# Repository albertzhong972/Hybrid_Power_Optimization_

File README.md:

# Hybrid-Power-Optimization
ECEN 404 Senior Design - Hybrid Power Optimization

Project Description:
We are combining DC power from a solar panel with AC power from the grid to provide power to a load. We are using a PIC32MK microcontroller in this project.

There are four subsystems:
  -Power (Antonio)
  -PCB (Albert)
  -Software/Firmware (Eduardo)
  -Feedback (Heraclio)

  You can find our individual work as well as our progress reports in our own folders.

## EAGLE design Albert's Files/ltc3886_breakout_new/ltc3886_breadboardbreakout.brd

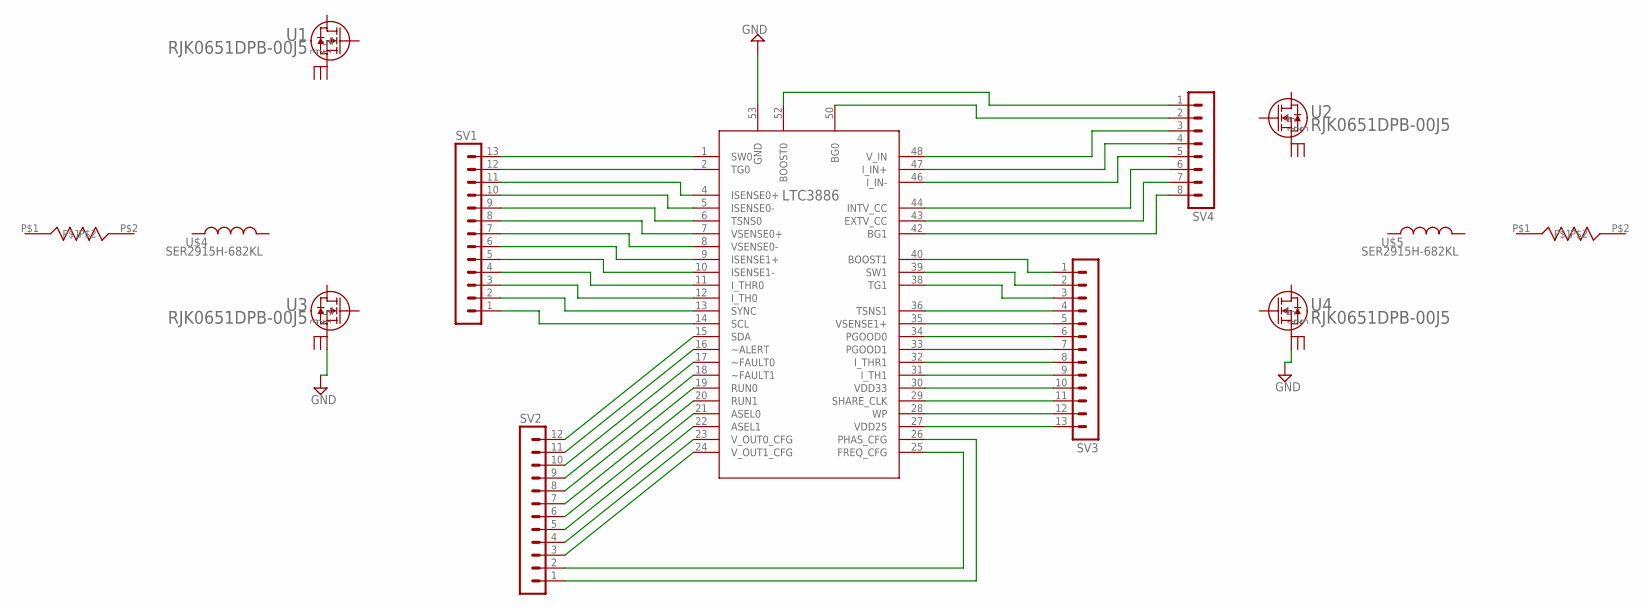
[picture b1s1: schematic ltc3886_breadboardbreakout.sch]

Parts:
GND: LTC3886; QFN-52_UKG_2
SV1, SV3: MA13-1
SV2: MA12-1
SV4: MA08-1
U1, U2, U3, U4: RJK0651DPB-00J5; LFPAK
U$2, U$3: CSS2H-2512K-2L00FE
U$4, U$5: SER2915H-682KL

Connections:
GND: GND.53 (GND), U3.1, U4.1
unnamed: GND.1 (SW0), SV1.13
unnamed: GND.2 (TG0), SV1.12
unnamed: GND.4 (ISENSE0+), SV1.11
unnamed: GND.5 (ISENSE0-), SV1.10
unnamed: GND.6 (TSNS0), SV1.9
unnamed: GND.7 (VSENSE0+), SV1.8
unnamed: GND.8 (VSENSE0-), SV1.7
unnamed: GND.9 (ISENSE1+), SV1.6
unnamed: GND.10 (ISENSE1-), SV1.5
unnamed: GND.11 (I_THR0), SV1.4
unnamed: GND.12 (I_TH0), SV1.3
unnamed: GND.13 (SYNC), SV1.2
unnamed: GND.14 (SCL), SV1.1
unnamed: GND.24 (V_OUT1_CFG), SV2.3
unnamed: GND.23 (V_OUT0_CFG), SV2.4
unnamed: GND.22 (ASEL1), SV2.5
unnamed: GND.21 (ASEL0), SV2.6
unnamed: GND.20 (RUN1), SV2.7
unnamed: GND.19 (RUN0), SV2.8
unnamed: GND.18 (~FAULT1), SV2.9
unnamed: GND.17 (~FAULT0), SV2.10
unnamed: GND.16 (~ALERT), SV2.11
unnamed: GND.15 (SDA), SV2.12
unnamed: GND.25 (FREQ_CFG), SV2.2
unnamed: GND.26 (PHAS_CFG), SV2.1
unnamed: GND.27 (VDD25), SV3.13
unnamed: GND.28 (WP), SV3.12
unnamed: GND.29 (SHARE_CLK), SV3.11
unnamed: GND.30 (VDD33), SV3.10
unnamed: GND.31 (I_TH1), SV3.9
unnamed: GND.32 (I_THR1), SV3.8
unnamed: GND.33 (PGOOD1), SV3.7
unnamed: GND.34 (PGOOD0), SV3.6
unnamed: GND.35 (VSENSE1+), SV3.5
unnamed: GND.36 (TSNS1), SV3.4
unnamed: GND.38 (TG1), SV3.3
unnamed: GND.39 (SW1), SV3.2
unnamed: GND.40 (BOOST1), SV3.1
unnamed: GND.42 (BG1), SV4.8
unnamed: GND.43 (EXTV_CC), SV4.7
unnamed: GND.44 (INTV_CC), SV4.6
unnamed: GND.46 (I_IN-), SV4.5
unnamed: GND.47 (I_IN+), SV4.4
unnamed: GND.48 (V_IN), SV4.3
unnamed: GND.50 (BG0), SV4.2
unnamed: GND.52 (BOOST0), SV4.1

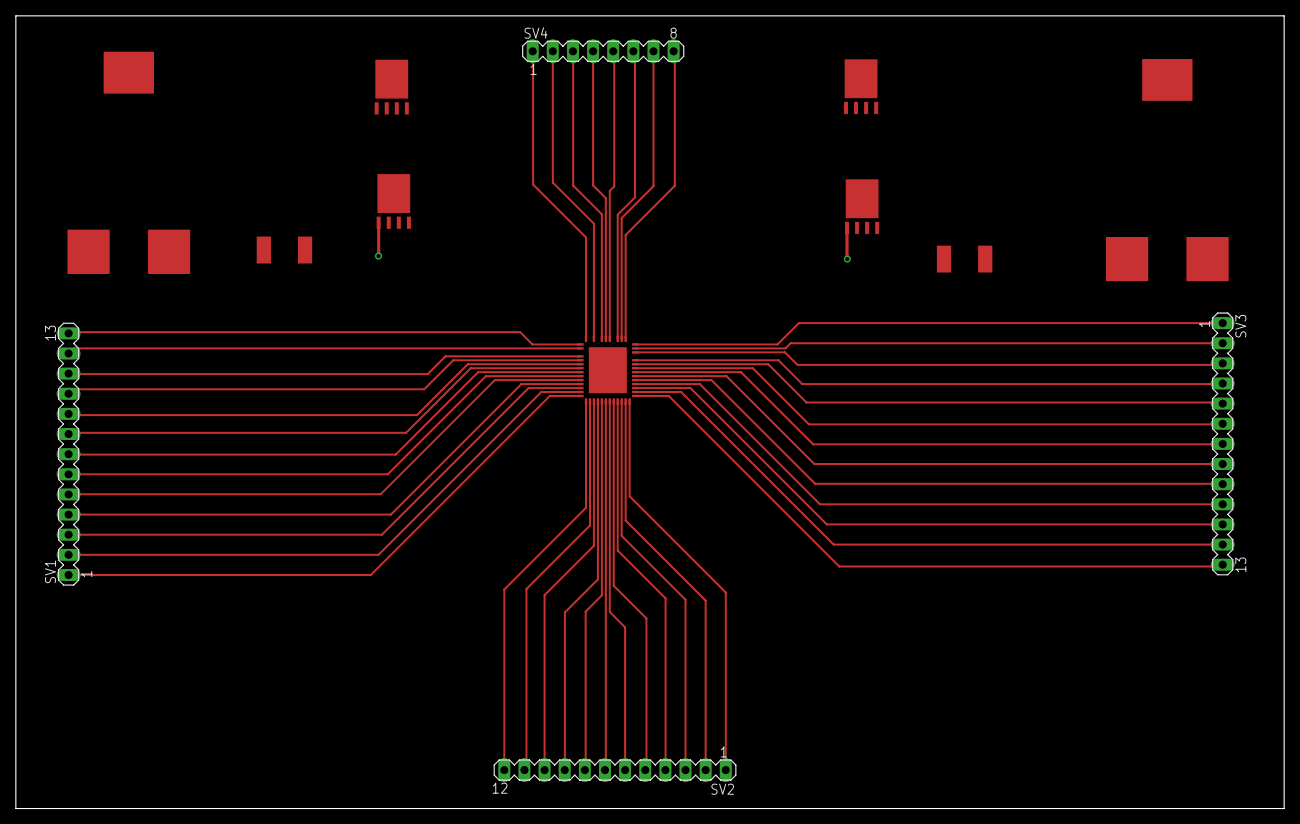
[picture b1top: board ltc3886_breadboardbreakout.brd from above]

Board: 2 copper layers, 160.0 x 100.0 mm, 13 parts (0 on the bottom side), 47 nets.

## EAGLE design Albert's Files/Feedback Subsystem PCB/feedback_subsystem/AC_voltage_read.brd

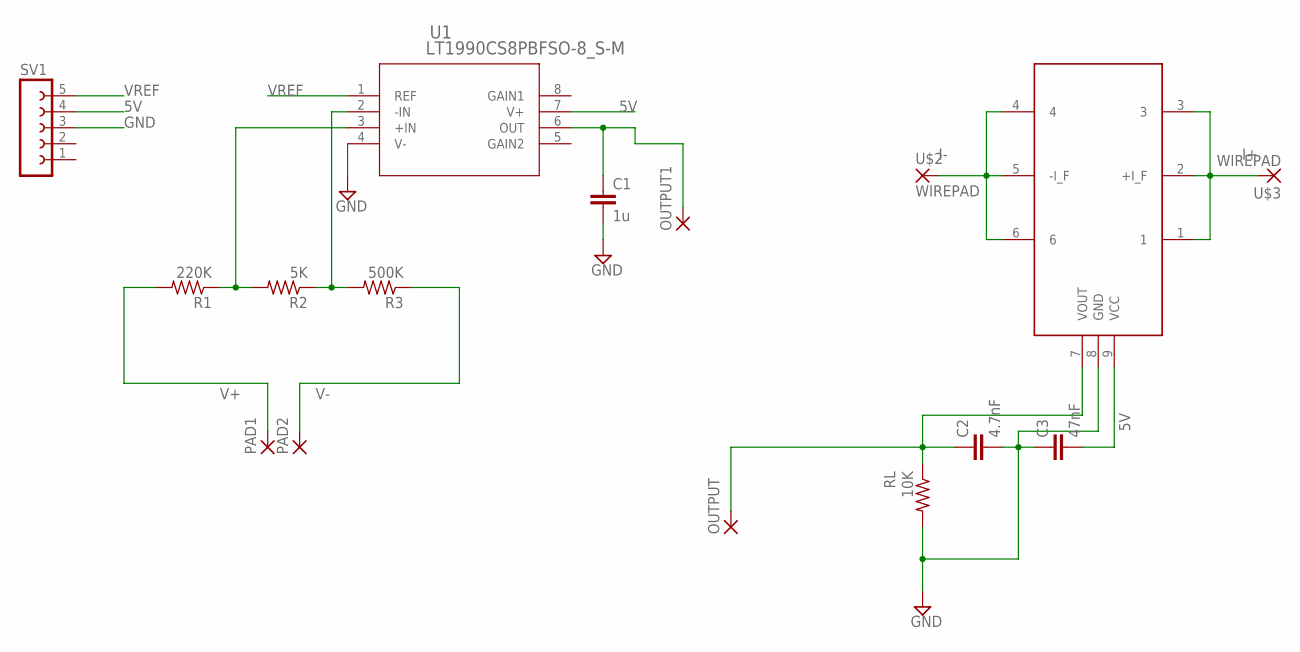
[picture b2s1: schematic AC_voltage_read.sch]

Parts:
C1: 1u; C075-032X103
C2: 4.7nF; C050-045X075
C3: 47nF; C050-045X075
OUTPUT, OUTPUT1: WIREPAD3,17/1,2; 3,17/1,2
PAD1, PAD2: 3,81/1,1
R1: 220K; 0207/12
R2: 5K; 0207/12
R3: 500K; 0207/12
RL: 10K; 0207/12
SV1: FE05-1
U1: LT1990CS8PBFSO-8_S-M; SO-8_S-M
U$1: S22P015S05; S22FOOTPRINT
U$2, U$3: WIREPAD

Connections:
5V: C3.2, SV1.4, U1.7 (V+), U$1.9 (VCC)
GND: C1.2, C2.2, C3.1, RL.2, SV1.3, U1.4 (V-), U$1.8 (GND)
I+: U$1.1, U$1.2 (+I_F), U$1.3, U$3.P$1
I-: U$1.4, U$1.5 (-I_F), U$1.6, U$2.P$1
unnamed: R2.1, R3.2, U1.2 (-IN)
unnamed: C1.1, OUTPUT1.1, U1.6 (OUT)
unnamed: C2.1, OUTPUT.1, RL.1, U$1.7 (VOUT)
unnamed: R1.1, R2.2, U1.3 (+IN)
V+: PAD1.1, R1.2
V-: PAD2.1, R3.1
VREF: SV1.5, U1.1 (REF)

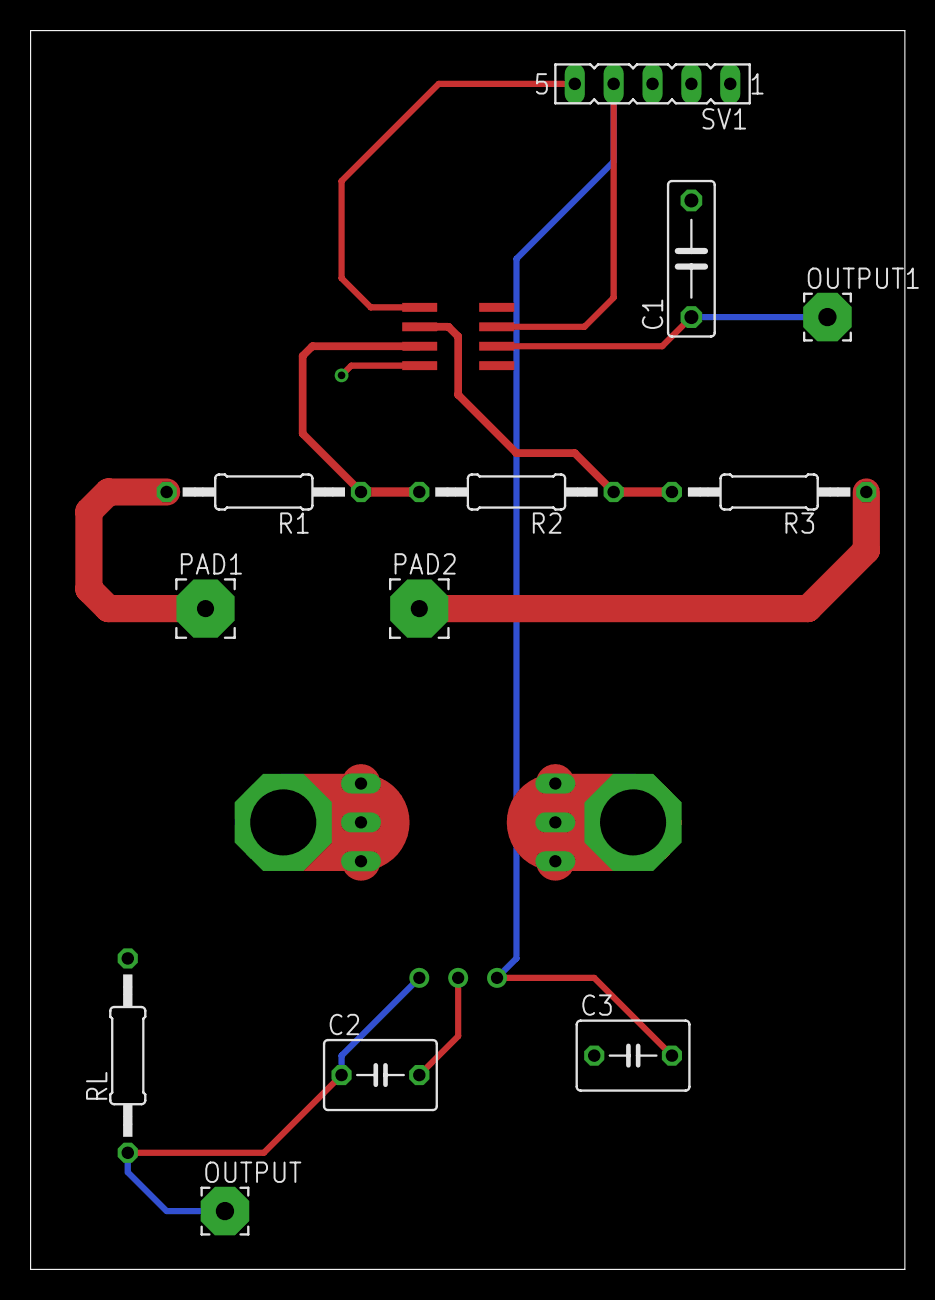
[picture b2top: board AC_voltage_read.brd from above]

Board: 2 copper layers, 57.1 x 80.9 mm, 16 parts (0 on the bottom side), 11 nets.

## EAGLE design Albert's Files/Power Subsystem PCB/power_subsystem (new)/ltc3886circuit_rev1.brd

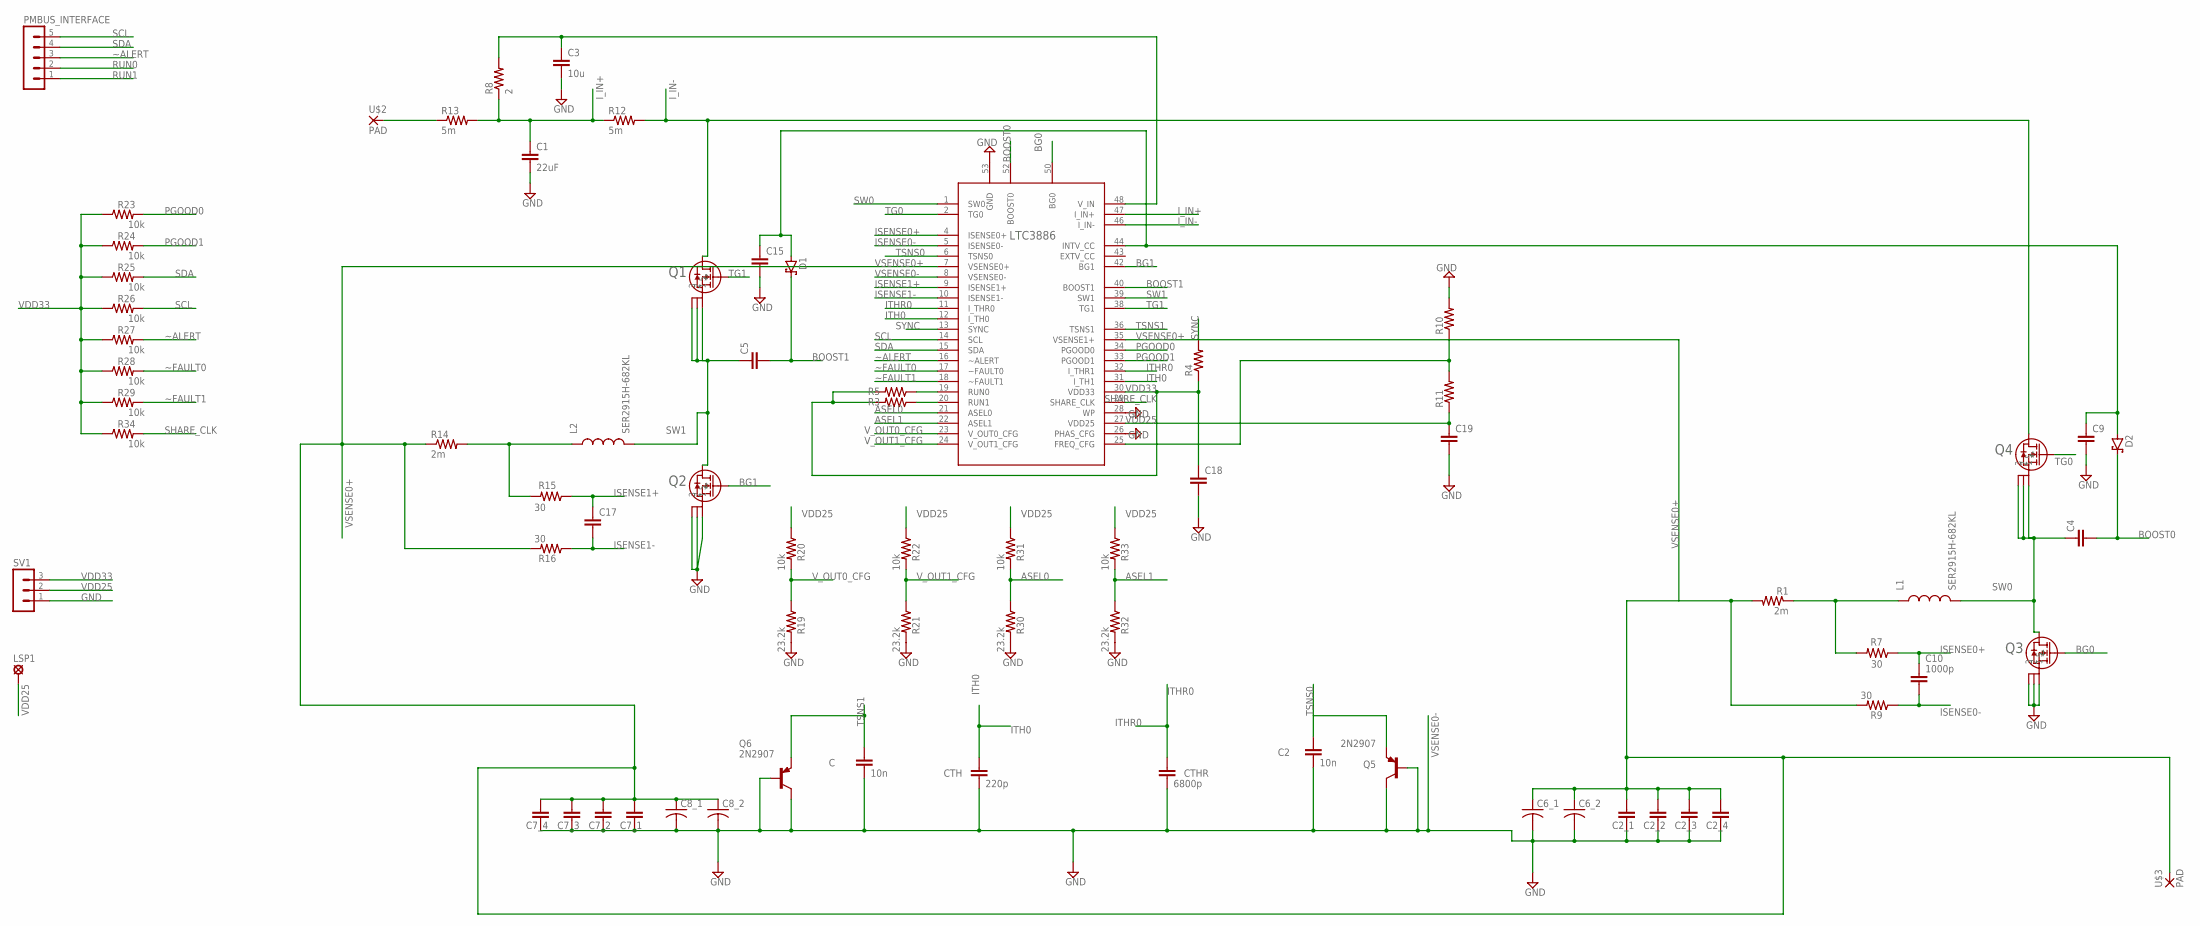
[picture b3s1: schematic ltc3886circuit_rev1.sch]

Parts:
C, C2: 10n; C075-032X103
C1: 22uF; ESK226M100AE3AA(22UF_CAP)
C2_1, C2_2, C2_3, C2_4, C7_1, C7_2, C7_3, C7_4: ESK226M100AE3AA(22UF_CAP)
C3: 10u; C075-032X103
C4, C5, C9, C15, C17, C18, C19: C-EU075-032X103; C075-032X103
C6_1, C6_2, C8_1, C8_2: C-US050-025X075; C050-025X075
C10: 1000p; C075-032X103
CTH: 220p; C075-032X103
CTHR: 6800p; C075-032X103
D1, D2: SCHOTTKY-DIODECB417-15; CB417-15
L1, L2: SER2915H-682KL
LSP1: MCS08
PMBUS_INTERFACE: MA05-1
Q1, Q2, Q3, Q4: RJK0651DPB-00J5; LFPAK
Q5, Q6: 2N2907; TO18
R1, R14: 2m; CSS2H-2512K-2L00FE
R3, R4, R5, R10, R11: R-US_0207/12; 0207/12
R7, R9, R15, R16: 30; 0207/12
R8: 2; ERJ-B1BF2R0U(2-OHM)
R12: 5m; CSS4J-4026K-5L00F(5M-OHM)
R13: 5m; CSS2H-2512K-2L00FE
R19, R21, R30, R32: 23.2k; 0207/12
R20, R22, R23, R24, R25, R26, R27, R28, R29, R31, R33, R34: 10k; 0207/12
SV1: MA03-1
U$1: LTC3886; QFN-52_UKG_2
U$2, U$3: PAD

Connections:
ASEL0: R30.1, R31.2, U$1.21 (ASEL0)
ASEL1: R32.1, R33.2, U$1.22 (ASEL1)
BG0: Q3.4, U$1.50 (BG0)
BG1: Q2.4, U$1.42 (BG1)
BOOST0: C4.2, D2.C, U$1.52 (BOOST0)
BOOST1: C5.2, D1.C, U$1.40 (BOOST1)
GND: C1.P$2 (2), C3.2, C9.2, C15.2, C18.2, C19.2, Q2.1, Q2.2, Q2.3, Q3.1, Q3.2, Q3.3, R10.2, R19.2, R21.2, R30.2, R32.2, SV1.1, U$1.26 (PHAS_CFG), U$1.28 (WP), U$1.53 (GND)
ISENSE0+: C10.1, R7.1, U$1.4 (ISENSE0+)
ISENSE0-: C10.2, R9.1, U$1.5 (ISENSE0-)
ISENSE1+: C17.1, R15.1, U$1.9 (ISENSE1+)
ISENSE1-: C17.2, R16.1, U$1.10 (ISENSE1-)
ITH0: CTH.1, U$1.12 (I_TH0), U$1.31 (I_TH1)
ITHR0: CTHR.1, U$1.11 (I_THR0), U$1.32 (I_THR1)
I_IN+: C1.P$1 (1), R8.P$1 (1), R12.P$1 (1), R13.P$2 (2), U$1.47 (I_IN+)
I_IN-: Q1.5, Q4.5, R12.P$2 (2), U$1.46 (I_IN-)
unnamed: R5.1, U$1.19 (RUN0)
unnamed: R3.1, U$1.20 (RUN1)
unnamed: L2.P$1 (1), R14.P$2 (2), R15.2
unnamed: C9.1, C15.1, D1.A, D2.A, U$1.44 (INTV_CC)
unnamed: L1.P$1 (1), R1.P$1 (1), R7.2
unnamed: R13.P$1 (1), U$2.P$1
unnamed: C3.1, R8.P$2 (2), U$1.48 (V_IN)
unnamed: R10.1, R11.2, U$1.25 (FREQ_CFG)
PGOOD0: R23.2, U$1.34 (PGOOD0)
PGOOD1: R24.2, U$1.33 (PGOOD1)
RUN0: PMBUS_INTERFACE.2
RUN1: PMBUS_INTERFACE.1
SCL: PMBUS_INTERFACE.5, R26.2, U$1.14 (SCL)
SDA: PMBUS_INTERFACE.4, R25.2, U$1.15 (SDA)
SHARE_CLK: R34.2, U$1.29 (SHARE_CLK)
SW0: C4.1, L1.P$2 (2), Q3.5, Q4.1, Q4.2, Q4.3, U$1.1 (SW0)
SW1: C5.1, L2.P$2 (2), Q1.1, Q1.2, Q1.3, Q2.5, U$1.39 (SW1)
SYNC: R4.2, U$1.13 (SYNC)
TG0: Q4.4, U$1.2 (TG0)
TG1: Q1.4, U$1.38 (TG1)
TSNS0: C2.1, Q5.1 (E), U$1.6 (TSNS0)
TSNS1: C.1, Q6.1 (E), U$1.36 (TSNS1)
VDD25: C19.1, LSP1.MP, R11.1, R20.1, R22.1, R31.1, R33.1, SV1.2, U$1.27 (VDD25)
VDD33: C18.1, R3.2, R4.1, R5.2, R23.1, R24.1, R25.1, R26.1, R27.1, R28.1, R29.1, R34.1, SV1.3, U$1.30 (VDD33)
VSENSE0+: C2_1.P$1 (1), C2_2.P$1 (1), C2_3.P$1 (1), C2_4.P$1 (1), C6_1.1, C6_2.1, C7_1.P$1 (1), C7_2.P$1 (1), C7_3.P$1 (1), C7_4.P$1 (1), C8_1.1, C8_2.1, R1.P$2 (2), R9.2, R14.P$1 (1), R16.2, U$1.7 (VSENSE0+), U$1.35 (VSENSE1+), U$3.P$1
VSENSE0-: C.2, C2.2, C2_1.P$2 (2), C2_2.P$2 (2), C2_3.P$2 (2), C2_4.P$2 (2), C6_1.2, C6_2.2, C7_1.P$2 (2), C7_2.P$2 (2), C7_3.P$2 (2), C7_4.P$2 (2), C8_1.2, C8_2.2, CTH.2, CTHR.2, Q5.2 (B), Q5.3 (C), Q6.2 (B), Q6.3 (C), U$1.8 (VSENSE0-)
V_OUT0_CFG: R19.1, R20.2, U$1.23 (V_OUT0_CFG)
V_OUT1_CFG: R21.1, R22.2, U$1.24 (V_OUT1_CFG)
~ALERT: PMBUS_INTERFACE.3, R27.2, U$1.16 (~ALERT)
~FAULT0: R28.2, U$1.17 (~FAULT0)
~FAULT1: R29.2, U$1.18 (~FAULT1)

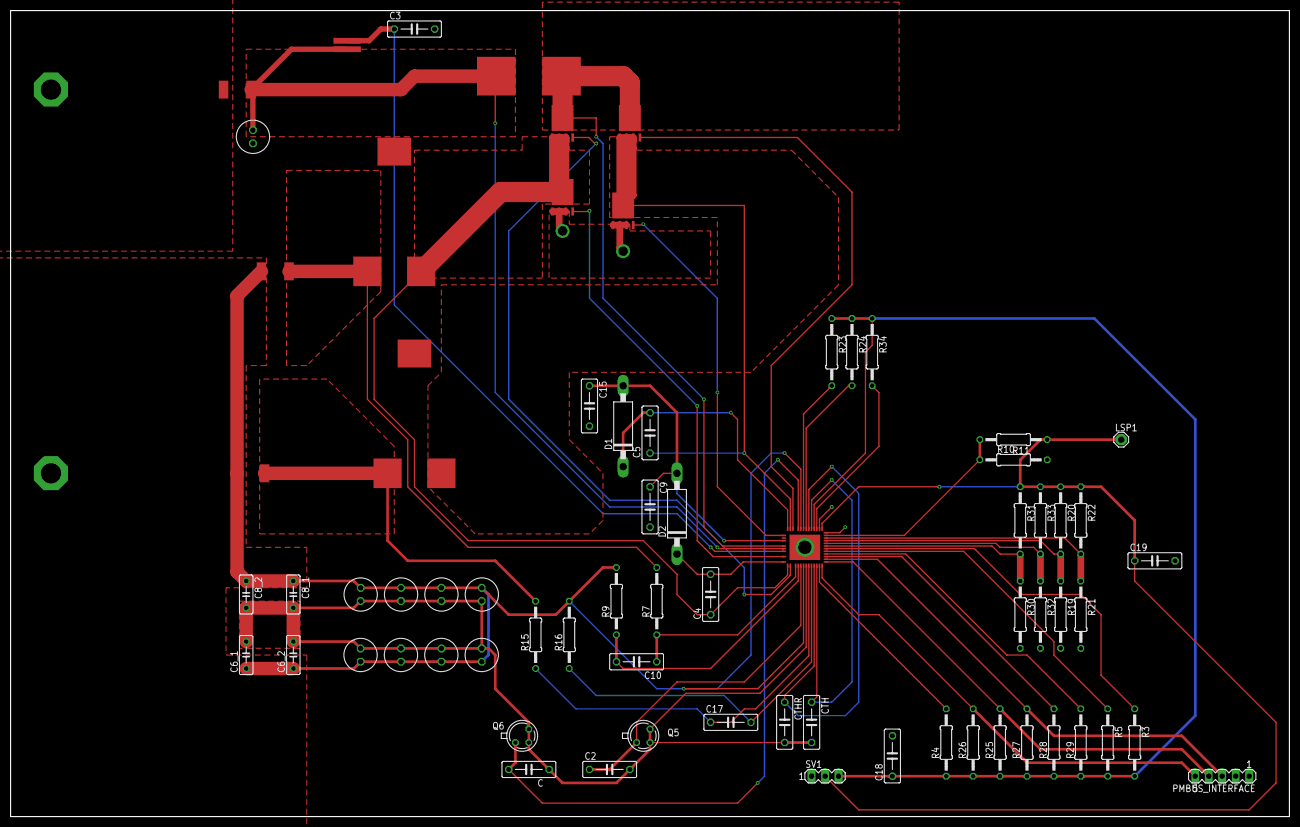
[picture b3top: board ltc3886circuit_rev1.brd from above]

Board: 2 copper layers, 241.3 x 152.1 mm, 72 parts (0 on the bottom side), 44 nets.

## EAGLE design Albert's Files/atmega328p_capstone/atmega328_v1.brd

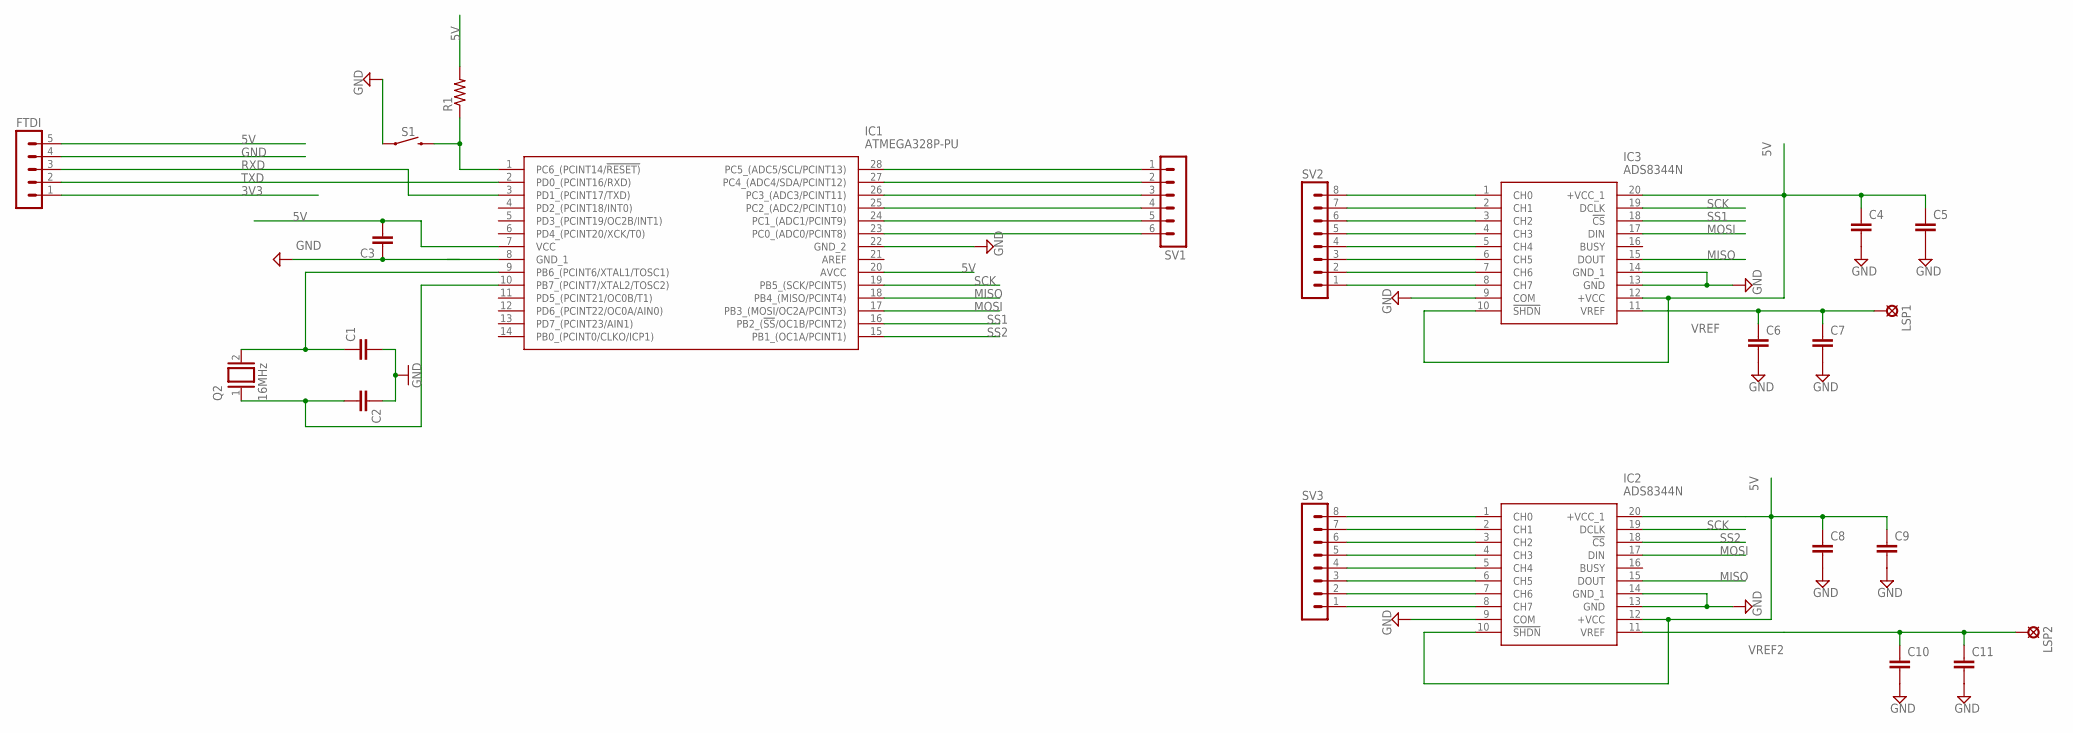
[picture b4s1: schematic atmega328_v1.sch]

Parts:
C1, C2, C3: C-EU025-050X050; C025-050X050
C4, C5, C6, C7, C8, C9, C10, C11: C-EU050-055X075; C050-055X075
FTDI: MA05-1
IC1: ATMEGA328P-PU; DIP794W53P254L3467H457Q28N
IC2, IC3: ADS8344N; SOP65P780X200-20N
LSP1, LSP2: SE11
Q2: 16MHz; QS
R1: R-US_0309/12; 0309/12
S1: MOMENTARY-SWITCH-SPST-SMD-5.2-REDUNDANT; TACTILE_SWITCH_SMD_5.2MM
SV1: MA06-1
SV2, SV3: MA08-1

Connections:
3V3: FTDI.1
5V: C3.2, C4.1, C5.1, C8.1, C9.1, FTDI.5, IC1.7 (VCC), IC1.20 (AVCC), IC2.10 (!SHDN), IC2.12 (+VCC), IC2.20 (+VCC_1), IC3.10 (!SHDN), IC3.12 (+VCC), IC3.20 (+VCC_1), R1.2
GND: C1.2, C2.1, C3.1, C4.2, C5.2, C6.2, C7.2, C8.2, C9.2, C10.2, C11.2, FTDI.4, IC1.22 (GND_2), IC2.9 (COM), IC2.13 (GND), IC2.14 (GND_1), IC3.9 (COM), IC3.13 (GND), IC3.14 (GND_1), S1.1, S1.2 (1)
MISO: IC1.18 (PB4_(MISO/PCINT4)), IC2.15 (DOUT), IC3.15 (DOUT)
MOSI: IC1.17 (PB3_(MOSI/OC2A/PCINT3)), IC2.17 (DIN), IC3.17 (DIN)
unnamed: IC3.1 (CH0), SV2.8
unnamed: IC1.28 (PC5_(ADC5/SCL/PCINT13)), SV1.1
unnamed: IC1.27 (PC4_(ADC4/SDA/PCINT12)), SV1.2
unnamed: C1.1, IC1.9 (PB6_(PCINT6/XTAL1/TOSC1)), Q2.2
unnamed: C2.2, IC1.10 (PB7_(PCINT7/XTAL2/TOSC2)), Q2.1
unnamed: IC1.26 (PC3_(ADC3/PCINT11)), SV1.3
unnamed: IC1.25 (PC2_(ADC2/PCINT10)), SV1.4
unnamed: IC1.24 (PC1_(ADC1/PCINT9)), SV1.5
unnamed: IC1.23 (PC0_(ADC0/PCINT8)), SV1.6
unnamed: IC1.1 (PC6_(PCINT14/!RESET)), R1.1, S1.3 (2), S1.4 (2)
unnamed: IC3.2 (CH1), SV2.7
unnamed: IC3.3 (CH2), SV2.6
unnamed: IC3.4 (CH3), SV2.5
unnamed: IC3.5 (CH4), SV2.4
unnamed: IC3.6 (CH5), SV2.3
unnamed: IC3.7 (CH6), SV2.2
unnamed: IC3.8 (CH7), SV2.1
unnamed: IC2.1 (CH0), SV3.8
unnamed: IC2.2 (CH1), SV3.7
unnamed: IC2.3 (CH2), SV3.6
unnamed: IC2.4 (CH3), SV3.5
unnamed: IC2.5 (CH4), SV3.4
unnamed: IC2.6 (CH5), SV3.3
unnamed: IC2.7 (CH6), SV3.2
unnamed: IC2.8 (CH7), SV3.1
RXD: FTDI.3, IC1.3 (PD1_(PCINT17/TXD))
SCK: IC1.19 (PB5_(SCK/PCINT5)), IC2.19 (DCLK), IC3.19 (DCLK)
SS1: IC1.16 (PB2_(!SS!/OC1B/PCINT2)), IC3.18 (!CS)
SS2: IC1.15 (PB1_(OC1A/PCINT1)), IC2.18 (!CS)
TXD: FTDI.2, IC1.2 (PD0_(PCINT16/RXD))
VREF: C6.1, C7.1, IC3.11 (VREF), LSP1.MP
VREF2: C10.1, C11.1, IC2.11 (VREF), LSP2.MP

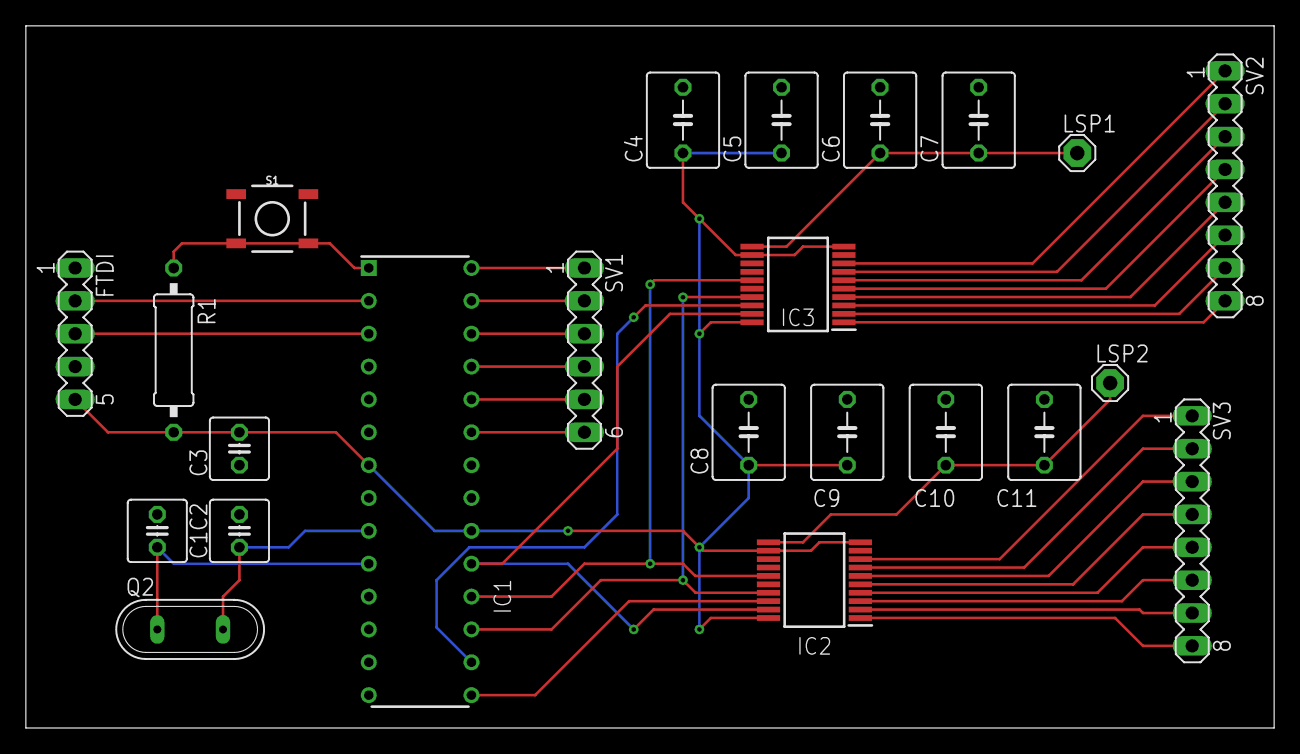
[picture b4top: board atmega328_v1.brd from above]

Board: 2 copper layers, 96.5 x 54.3 mm, 23 parts (0 on the bottom side), 36 nets.

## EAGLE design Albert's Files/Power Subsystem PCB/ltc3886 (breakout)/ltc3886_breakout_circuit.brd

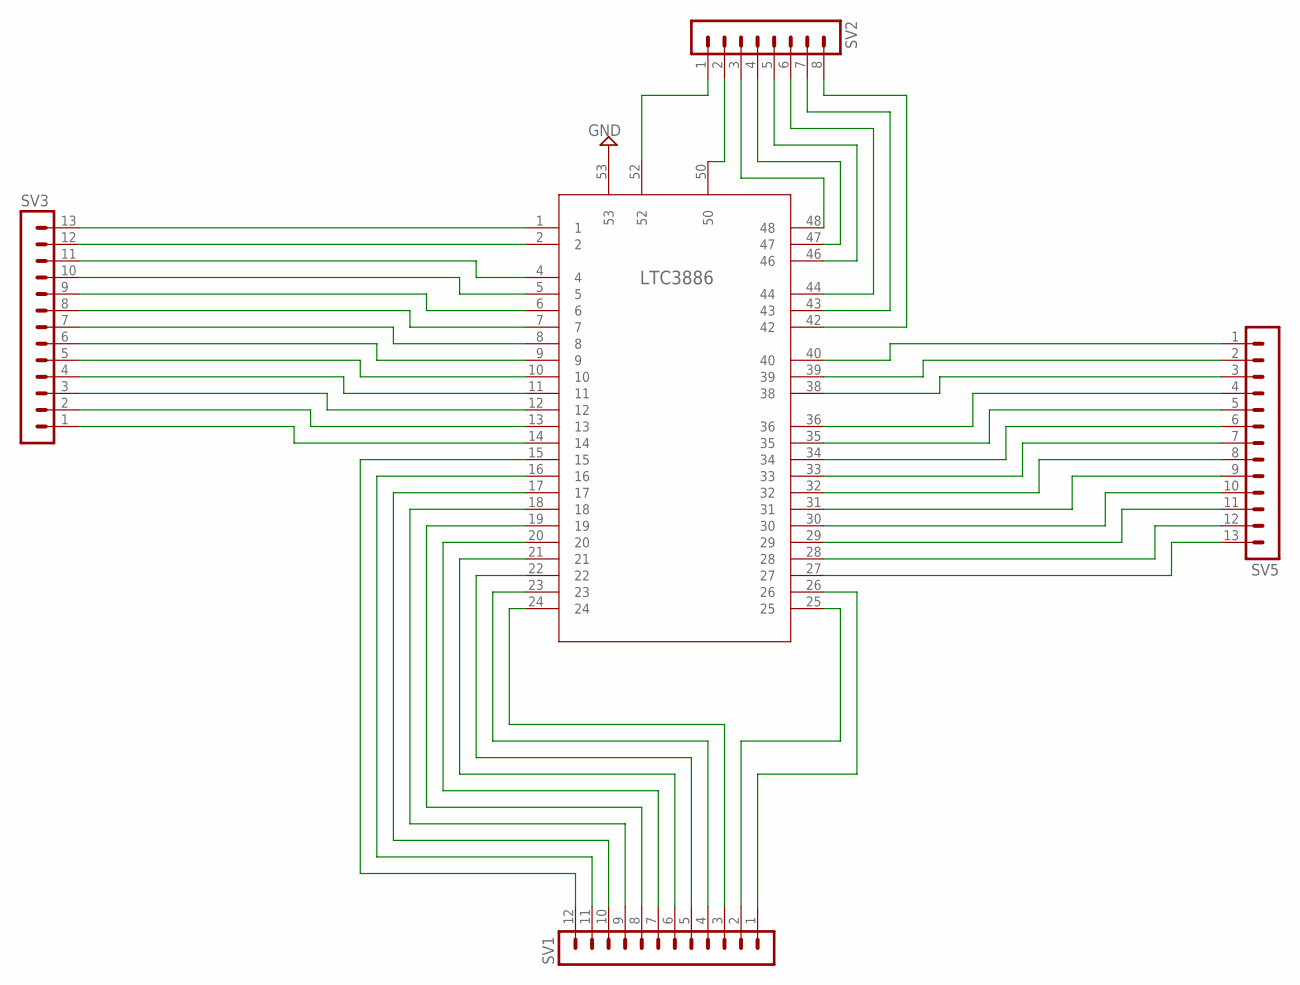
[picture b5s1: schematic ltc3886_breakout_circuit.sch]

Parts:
SV1: MA12-1
SV2: MA08-1
SV3, SV5: MA13-1
U$1: LTC3886; QFN-52_UKG_2

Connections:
GND: U$1.53
unnamed: SV3.13, U$1.1
unnamed: SV3.12, U$1.2
unnamed: SV3.11, U$1.4
unnamed: SV3.10, U$1.5
unnamed: SV3.9, U$1.6
unnamed: SV3.8, U$1.7
unnamed: SV3.7, U$1.8
unnamed: SV3.6, U$1.9
unnamed: SV3.5, U$1.10
unnamed: SV3.4, U$1.11
unnamed: SV3.3, U$1.12
unnamed: SV3.2, U$1.13
unnamed: SV3.1, U$1.14
unnamed: SV1.12, U$1.15
unnamed: SV1.11, U$1.16
unnamed: SV1.10, U$1.17
unnamed: SV1.9, U$1.18
unnamed: SV1.8, U$1.19
unnamed: SV1.7, U$1.20
unnamed: SV1.6, U$1.21
unnamed: SV2.3, U$1.48
unnamed: SV2.4, U$1.47
unnamed: SV2.5, U$1.46
unnamed: SV2.6, U$1.44
unnamed: SV2.7, U$1.43
unnamed: SV2.8, U$1.42
unnamed: SV5.1, U$1.40
unnamed: SV5.2, U$1.39
unnamed: SV5.3, U$1.38
unnamed: SV5.4, U$1.36
unnamed: SV5.5, U$1.35
unnamed: SV5.6, U$1.34
unnamed: SV5.7, U$1.33
unnamed: SV5.8, U$1.32
unnamed: SV5.9, U$1.31
unnamed: SV5.10, U$1.30
unnamed: SV5.11, U$1.29
unnamed: SV5.12, U$1.28
unnamed: SV5.13, U$1.27
unnamed: SV1.1, U$1.26
unnamed: SV1.5, U$1.22
unnamed: SV1.4, U$1.23
unnamed: SV1.3, U$1.24
unnamed: SV1.2, U$1.25
unnamed: SV2.1, U$1.52
unnamed: SV2.2, U$1.50

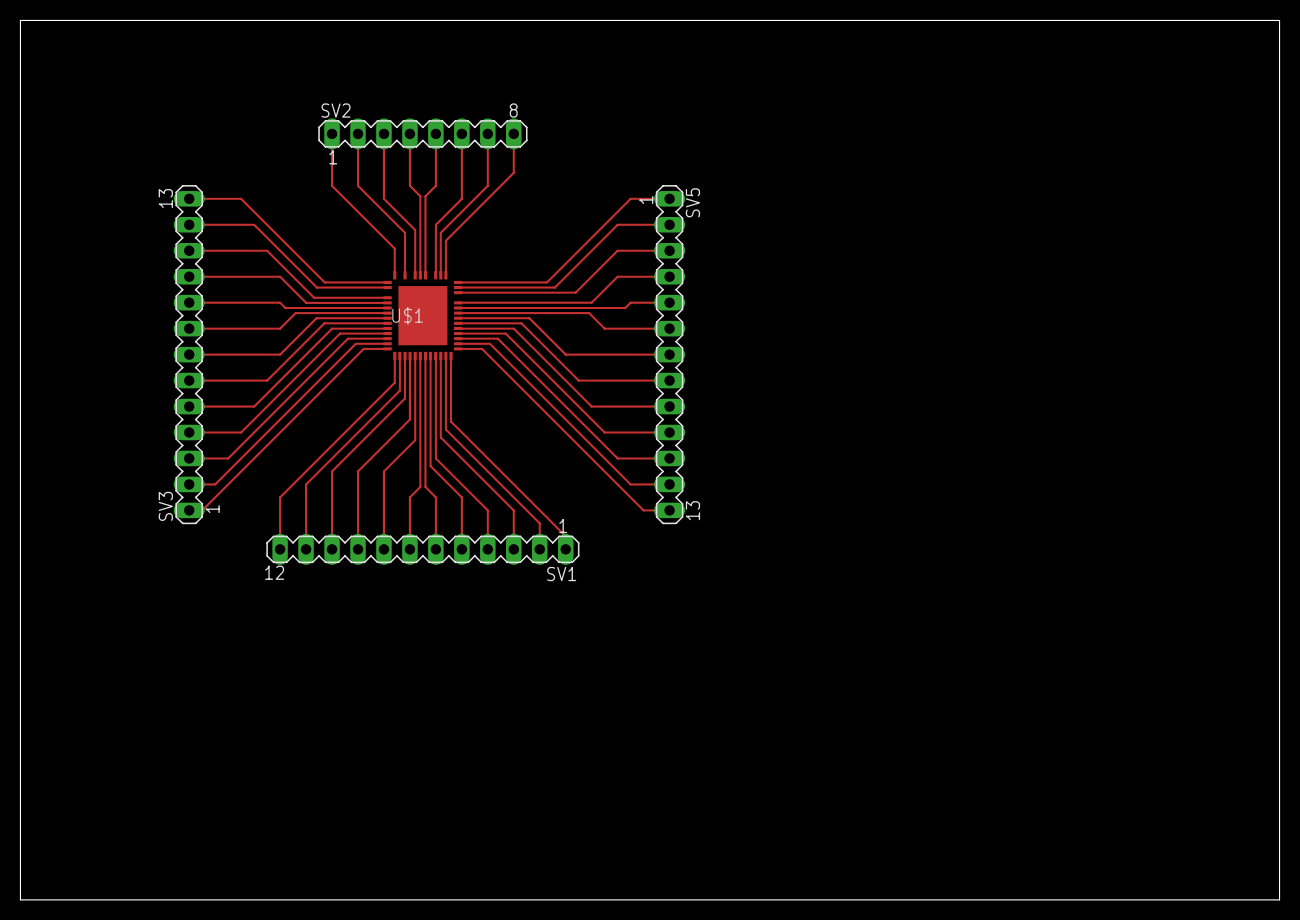
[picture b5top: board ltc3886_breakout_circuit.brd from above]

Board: 2 copper layers, 123.2 x 86.0 mm, 5 parts (0 on the bottom side), 46 nets.

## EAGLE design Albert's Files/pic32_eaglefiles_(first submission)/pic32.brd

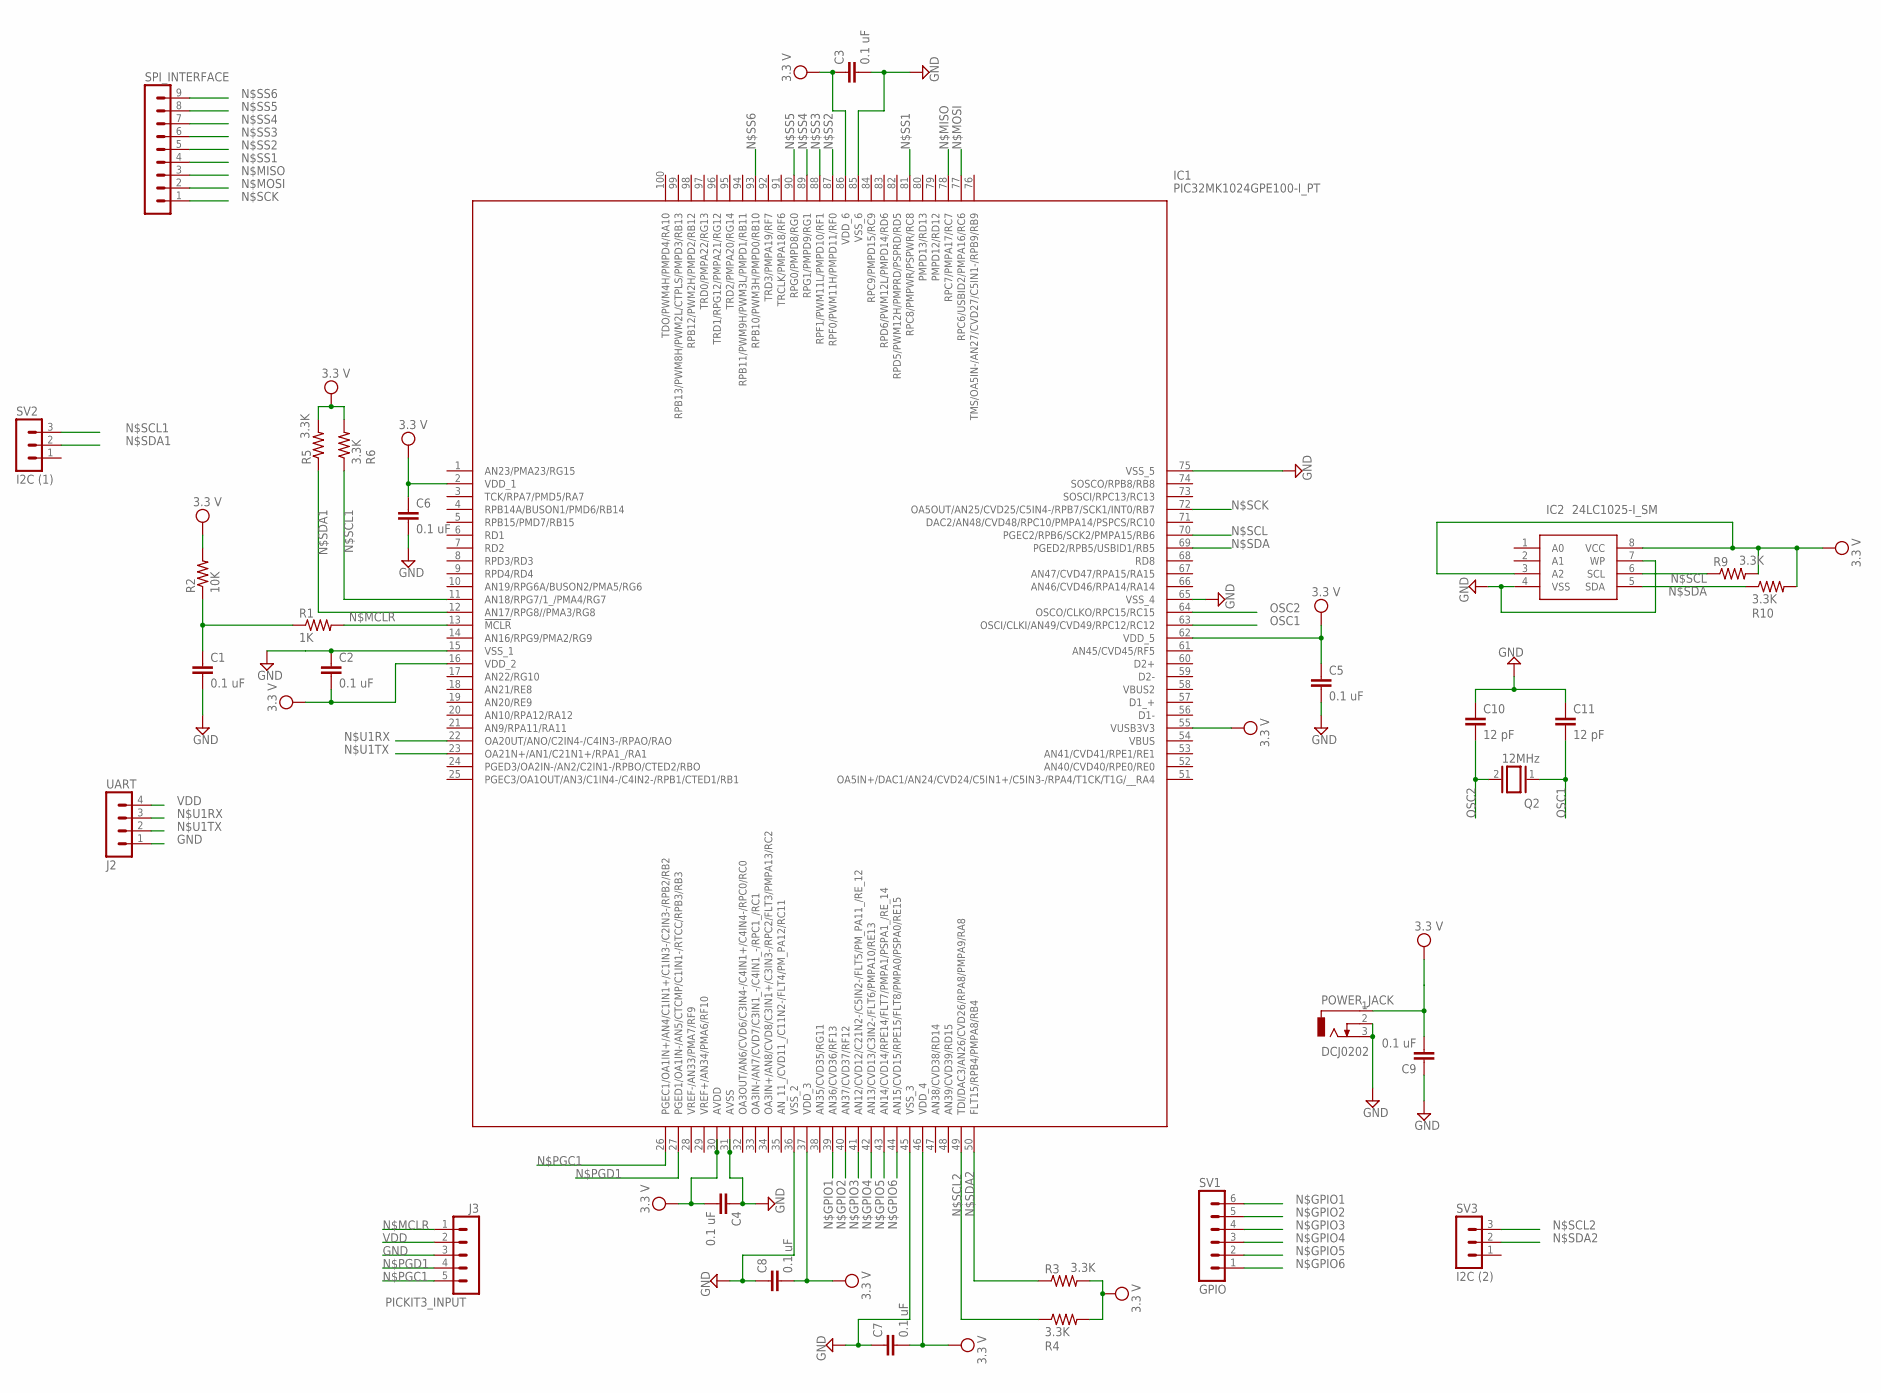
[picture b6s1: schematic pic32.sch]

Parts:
C1, C2, C3, C4, C5, C6, C7, C8, C9: 0.1 uF; C025-025X050
C10, C11: 12 pF; C025-025X050
IC1: PIC32MK1024GPE100-I_PT; QFP40P1400X1400X120-100N
IC2: 24LC1025-I_SM; SOIC127P794X203-8N
PICKIT3_INPUT: J3; MA05-1
POWER_JACK: DCJ0202
Q2: 12MHz; QS
R1: 1K; 0207/7
R2: 10K; 0207/7
R3, R4, R5, R6, R9, R10: 3.3K; 0207/7
SPI_INTERFACE: J1; MA09-1
SV1: GPIO; MA06-1
SV2: I2C (1); MA03-1
SV3: I2C (2); MA03-1
UART: J2; MA04-1

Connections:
GND: C1.2, C2.1, C3.2, C4.1, C5.2, C6.2, C7.1, C8.1, C9.1, C10.1, C11.1, IC1.15 (VSS_1), IC1.31 (AVSS), IC1.36 (VSS_2), IC1.45 (VSS_3), IC1.65 (VSS_4), IC1.75 (VSS_5), IC1.85 (VSS_6), IC2.4 (VSS), IC2.7 (WP), PICKIT3_INPUT.3, POWER_JACK.2, POWER_JACK.3, UART.1
unnamed: C1.1, R1.1, R2.1
N$GPIO1: IC1.39 (AN36/CVD36/RF13), SV1.6
N$GPIO2: IC1.40 (AN37/CVD37/RF12), SV1.5
N$GPIO3: IC1.41 (AN12/CVD12/C21N2-/C5IN2-/FLT5/PM_PA11_/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), SV1.4
N$GPIO4: IC1.42 (AN13/CVD13/C3IN2-/FLT6/PMPA10/RE13), SV1.3
N$GPIO5: IC1.43 (AN14/CVD14/RPE14/FLT7/PMPA1/PSPA1_/RE_14), SV1.2
N$GPIO6: IC1.44 (AN15/CVD15/RPE15/FLT8/PMPA0/PSPA0/RE15), SV1.1
N$MCLR: IC1.13 (!MCLR), PICKIT3_INPUT.1, R1.2
N$MISO: IC1.78 (RPC7/PMPA17/RC7), SPI_INTERFACE.3
N$MOSI: IC1.77 (RPC6/USBID2/PMPA16/RC6), SPI_INTERFACE.2
N$PGC1: IC1.26 (PGEC1/OA1IN+/AN4/C1IN1+/C1IN3-/C2IN3-/R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), PICKIT3_INPUT.5
N$PGD1: IC1.27 (PGED1/OA1IN-/AN5/CTCMP/C1IN1-/RTCC/RPB3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), PICKIT3_INPUT.4
N$SCK: IC1.72 (OA5OUT/AN25/CVD25/C5IN4-/RPB7/SCK1/INT0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), SPI_INTERFACE.1
N$SCL: IC1.70 (PGEC2/RPB6/SCK2/PMPA15/RB6), IC2.6 (SCL), R9.1
N$SCL1: IC1.11 (AN18/RPG7/1_/PMA4/RG7), R6.1, SV2.3
N$SCL2: IC1.49 (TDI/DAC3/AN26/CVD26/RPA8/PMPA9/RA8), R4.1, SV3.3
N$SDA: IC1.69 (PGED2/RPB5/USBID1/RB5), IC2.5 (SDA), R10.1
N$SDA1: IC1.12 (AN17/RPG8//PMA3/RG8), R5.1, SV2.2
N$SDA2: IC1.50 (FLT15/RPB4/PMPA8/RB4), R3.1, SV3.2
N$SS1: IC1.81 (RPC8/PMPWR/PSPWR/RC8), SPI_INTERFACE.4
N$SS2: IC1.87 (RPF0/PWM11H/PMPD11/RF0), SPI_INTERFACE.5
N$SS3: IC1.88 (RPF1/PWM11L/PMPD10/RF1), SPI_INTERFACE.6
N$SS4: IC1.89 (RPG1/PMPD9/RG1), SPI_INTERFACE.7
N$SS5: IC1.90 (RPG0/PMPD8/RG0), SPI_INTERFACE.8
N$SS6: IC1.93 (RPB10/PWM3H/PMPD0/RB10), SPI_INTERFACE.9
N$U1RX: IC1.22 (OA20UT/ANO/C2IN4-/C4IN3-/RPAO/RAO), UART.3
N$U1TX: IC1.23 (OA21N+/AN1/C21N1+/RPA1_/RA1), UART.2
OSC1: C11.2, IC1.63 (OSCI/CLKI/AN49/CVD49/RPC12/RC12), Q2.1
OSC2: C10.2, IC1.64 (OSCO/CLKO/RPC15/RC15), Q2.2
VDD: C2.2, C3.1, C4.2, C5.1, C6.1, C7.2, C8.2, C9.2, IC1.2 (VDD_1), IC1.16 (VDD_2), IC1.30 (AVDD), IC1.37 (VDD_3), IC1.46 (VDD_4), IC1.55 (VUSB3V3), IC1.62 (VDD_5), IC1.86 (VDD_6), IC2.3 (A2), IC2.8 (VCC), PICKIT3_INPUT.2, POWER_JACK.1, R2.2, R3.2, R4.2, R5.2, R6.2, R9.2, R10.2, UART.4

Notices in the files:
parts and their libraries:
SparkFun-Switches: Licensing: Creative Commons ShareAlike 4.0 International - https://creativecommons.org/licenses/by-sa/4.0
